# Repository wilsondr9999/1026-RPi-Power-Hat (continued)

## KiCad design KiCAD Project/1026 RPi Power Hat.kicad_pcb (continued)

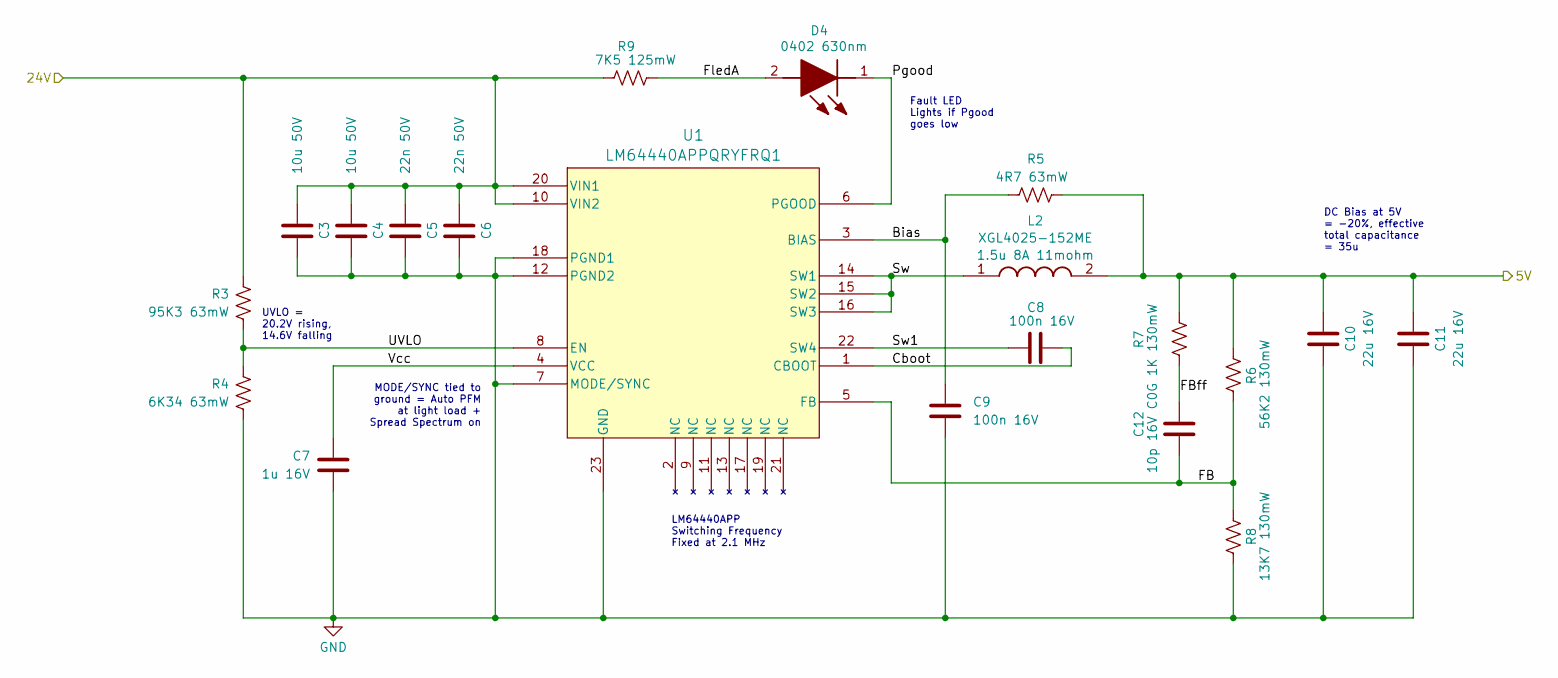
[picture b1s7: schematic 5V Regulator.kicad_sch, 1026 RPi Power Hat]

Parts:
C3, C4: GRJ32ER71H106KE11K; C_1210_3225Metric; Manufacturer_Part_Number GRJ32ER71H106KE11K; Mouser Part Number 81-GRJ32ER71H106KE1K
C5, C6: GCM155R71H223KA55D; C_0402_1005Metric; Manufacturer_Part_Number GCM155R71H223KA55D; Mouser Part Number 81-GCM155R71H223KA5D
C7: GCM188R71C105KA64J; C_0603_1608Metric; Manufacturer_Part_Number GCM188R71C105KA64J; Mouser Part Number 81-GCM188R71C105KA4J
C8, C9: GCM155R71C104KA55D; C_0402_1005Metric; Manufacturer_Part_Number GCM155R71C104KA55D; Mouser Part Number 81-GCM155R71C104KA5D
C10, C11: GCM32ER71C226ME19L; C_1210_3225Metric; Manufacturer_Part_Number GCM32ER71C226ME19L; Mouser Part Number 81-GCM32ER71C226ME9L
C12: VJ0402A100GXJCW1BC; C_0402_1005Metric; Manufacturer_Part_Number VJ0402A100GXJCW1BC; Mouser Part Number 77-VJ0402A100GXJCBC
D4: 150040RS73240; [D] Wurth Elektronik 150040RS73240; Mouser Part Number 710-150040RS73240
L2: XGL4025-152ME; [L] Coilcraft Inductor XGL4025; Manufacturer_Part_Number XGL4025-152ME
R3: 95K3; R_0402_1005Metric; Manufacturer_Part_Number CRCW040295K3FKED; Mouser Part Number 71-CRCW0402-95.3K-E3
R4: 6K34; R_0402_1005Metric; Manufacturer_Part_Number CRCW04026K34FKEDC; Mouser Part Number 71-CRCW04026K34FKEDC
R5: 4R7; R_0402_1005Metric; Manufacturer_Part_Number CRCW04024R70FNED; Mouser Part Number 71-CRCW04024R70FNED
R6: 56K2; R_0402_1005Metric; Manufacturer_Part_Number TNPW040256K2BEED; Mouser Part Number 71-TNPW040256K2BEED
R7: 1K; R_0402_1005Metric; Manufacturer_Part_Number TNPW04021K00BEED; Mouser Part Number 71-TNPW04021K00BEED
R8: 13K7; R_0402_1005Metric; Manufacturer_Part_Number TNPW040213K7BEED; Mouser Part Number 71-TNPW040213K7BEED
R9: 7K5; R_0402_1005Metric; Manufacturer_Part_Number RCC04027K50FKED; Mouser Part Number 71-RCC04027K50FKED
U1: LM64440APPQRYFRQ1; [U] TI LM63460 Sw Volt Reg; Manufacturer_Part_Number LM64440APPQRYFRQ1; Mouser Part Number 595-LM64440APPQRYRQ1

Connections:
/5V Regulator/5V: C10.1, C11.1, L2.2, R5.2, R6.1, R7.1; also elsewhere on the board
/5V Regulator/24V: C3.1, C4.1, C5.1, C6.1, R3.1, R9.1, U1.10 (VIN2), U1.20 (VIN1); also elsewhere on the board
/5V Regulator/Bias: C9.2, R5.1, U1.3 (BIAS)
/5V Regulator/Cboot: C8.2, U1.1 (CBOOT)
/5V Regulator/FB: C12.1, R6.2, R8.2, U1.5 (FB)
/5V Regulator/FBff: C12.2, R7.2
/5V Regulator/FledA: D4.2 (A), R9.2
/5V Regulator/Pgood: D4.1 (K), U1.6 (PGOOD)
/5V Regulator/Sw: L2.1, U1.14 (SW1), U1.15 (SW2), U1.16 (SW3)
/5V Regulator/Sw1: C8.1, U1.22 (SW4)
/5V Regulator/UVLO: R3.2, R4.1, U1.8 (EN)
/5V Regulator/Vcc: C7.1, U1.4 (VCC)
GND: C3.2, C4.2, C5.2, C6.2, C7.2, C9.1, C10.2, C11.2, R4.2, R8.1, U1.7 (MODE/SYNC), U1.12 (PGND2), U1.18 (PGND1), U1.23 (GND); also elsewhere on the board

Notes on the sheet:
MODE/SYNC tied to ground = Auto PFM at light load + Spread Spectrum on
Fault LED Lights if Pgood goes low
DC Bias at 5V = -20%, effective total capacitance = 35u
LM64440APP Switching Frequency Fixed at 2.1 MHz
UVLO = 20.2V rising, 14.6V falling

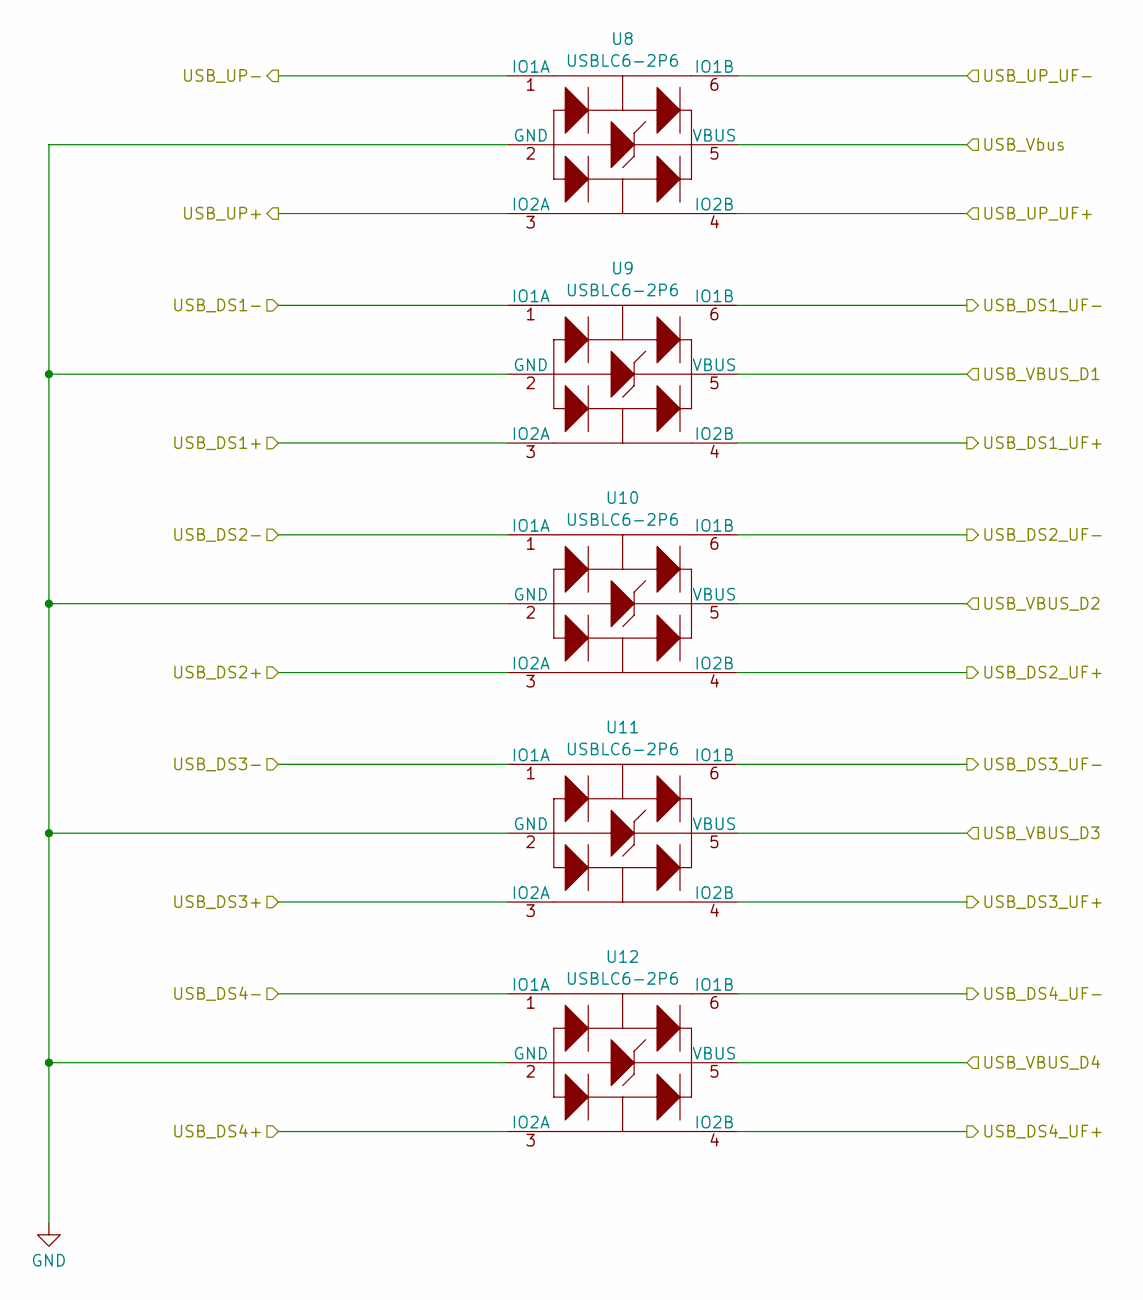
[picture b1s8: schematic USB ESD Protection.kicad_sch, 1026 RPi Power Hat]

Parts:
U8, U9, U10, U11, U12: USBLC6-2P6; [U] ST Micro USB ESD Protection USBLC6-2P6; Manufacturer_Part_Number USBLC6-2P6; Mouser Part Number 511-USBLC6-2P6

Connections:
/USB ESD Protection/USB_DS1_UF+: U9.4 (IO2B); also elsewhere on the board
/USB ESD Protection/USB_DS1_UF-: U9.6 (IO1B); also elsewhere on the board
/USB ESD Protection/USB_DS2_UF+: U10.4 (IO2B); also elsewhere on the board
/USB ESD Protection/USB_DS2_UF-: U10.6 (IO1B); also elsewhere on the board
/USB ESD Protection/USB_DS3_UF+: U11.4 (IO2B); also elsewhere on the board
/USB ESD Protection/USB_DS3_UF-: U11.6 (IO1B); also elsewhere on the board
/USB ESD Protection/USB_DS4_UF+: U12.4 (IO2B); also elsewhere on the board
/USB ESD Protection/USB_DS4_UF-: U12.6 (IO1B); also elsewhere on the board
/USB ESD Protection/USB_UP_UF+: U8.4 (IO2B); also elsewhere on the board
/USB ESD Protection/USB_UP_UF-: U8.6 (IO1B); also elsewhere on the board
/USB ESD Protection/USB_VBUS_D1: U9.5 (VBUS); also elsewhere on the board
/USB ESD Protection/USB_VBUS_D2: U10.5 (VBUS); also elsewhere on the board
/USB ESD Protection/USB_VBUS_D3: U11.5 (VBUS); also elsewhere on the board
/USB ESD Protection/USB_VBUS_D4: U12.5 (VBUS); also elsewhere on the board
/USB Hub/USB_DS1+: U9.3 (IO2A); also elsewhere on the board
/USB Hub/USB_DS1-: U9.1 (IO1A); also elsewhere on the board
/USB Hub/USB_DS2+: U10.3 (IO2A); also elsewhere on the board
/USB Hub/USB_DS2-: U10.1 (IO1A); also elsewhere on the board
/USB Hub/USB_DS3+: U11.3 (IO2A); also elsewhere on the board
/USB Hub/USB_DS3-: U11.1 (IO1A); also elsewhere on the board
/USB Hub/USB_DS4+: U12.3 (IO2A); also elsewhere on the board
/USB Hub/USB_DS4-: U12.1 (IO1A); also elsewhere on the board
/USB Hub/USB_UP+: U8.3 (IO2A); also elsewhere on the board
/USB Hub/USB_UP-: U8.1 (IO1A); also elsewhere on the board
/USB Hub/USB_Vbus: U8.5 (VBUS); also elsewhere on the board
GND: U8.2 (GND), U9.2 (GND), U10.2 (GND), U11.2 (GND), U12.2 (GND); also elsewhere on the board

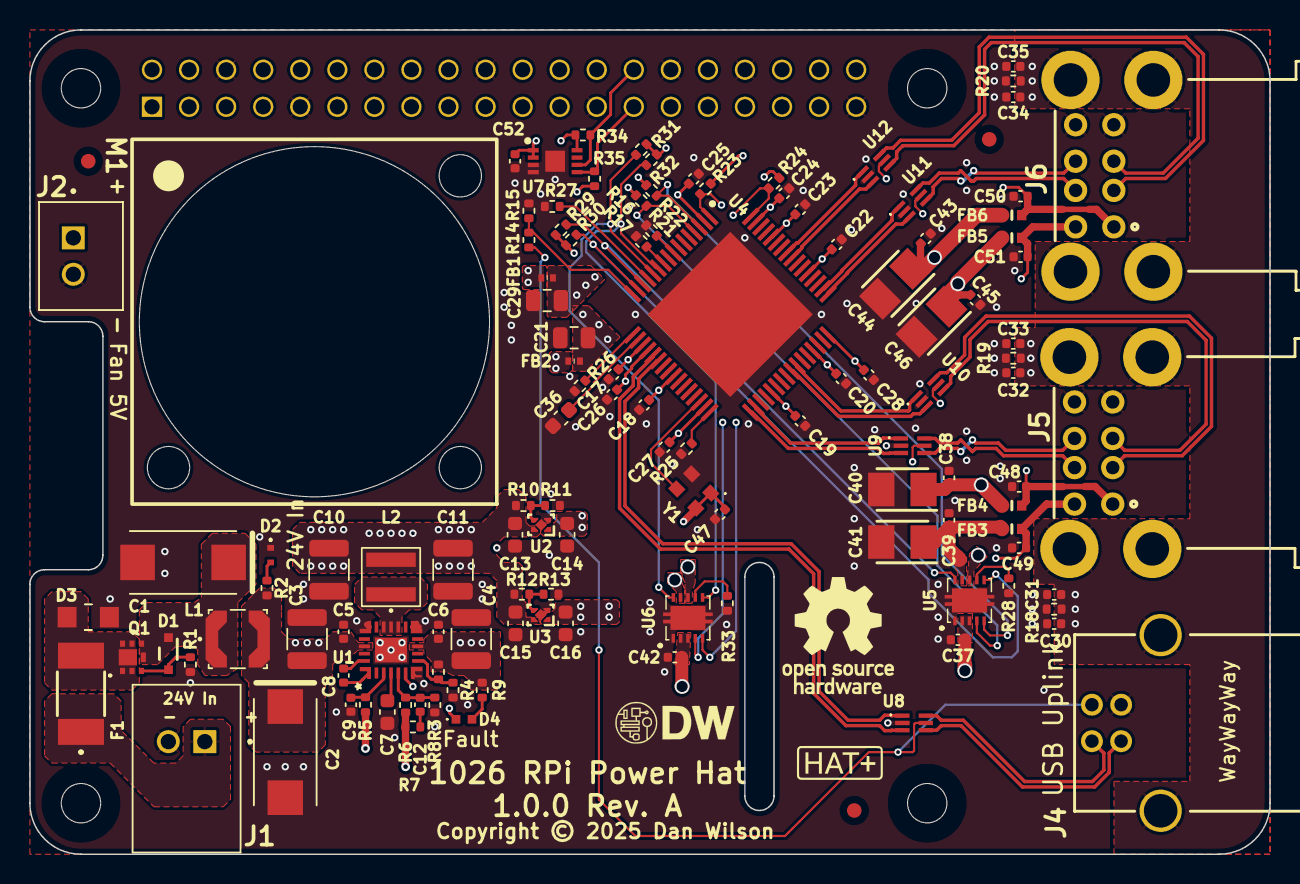
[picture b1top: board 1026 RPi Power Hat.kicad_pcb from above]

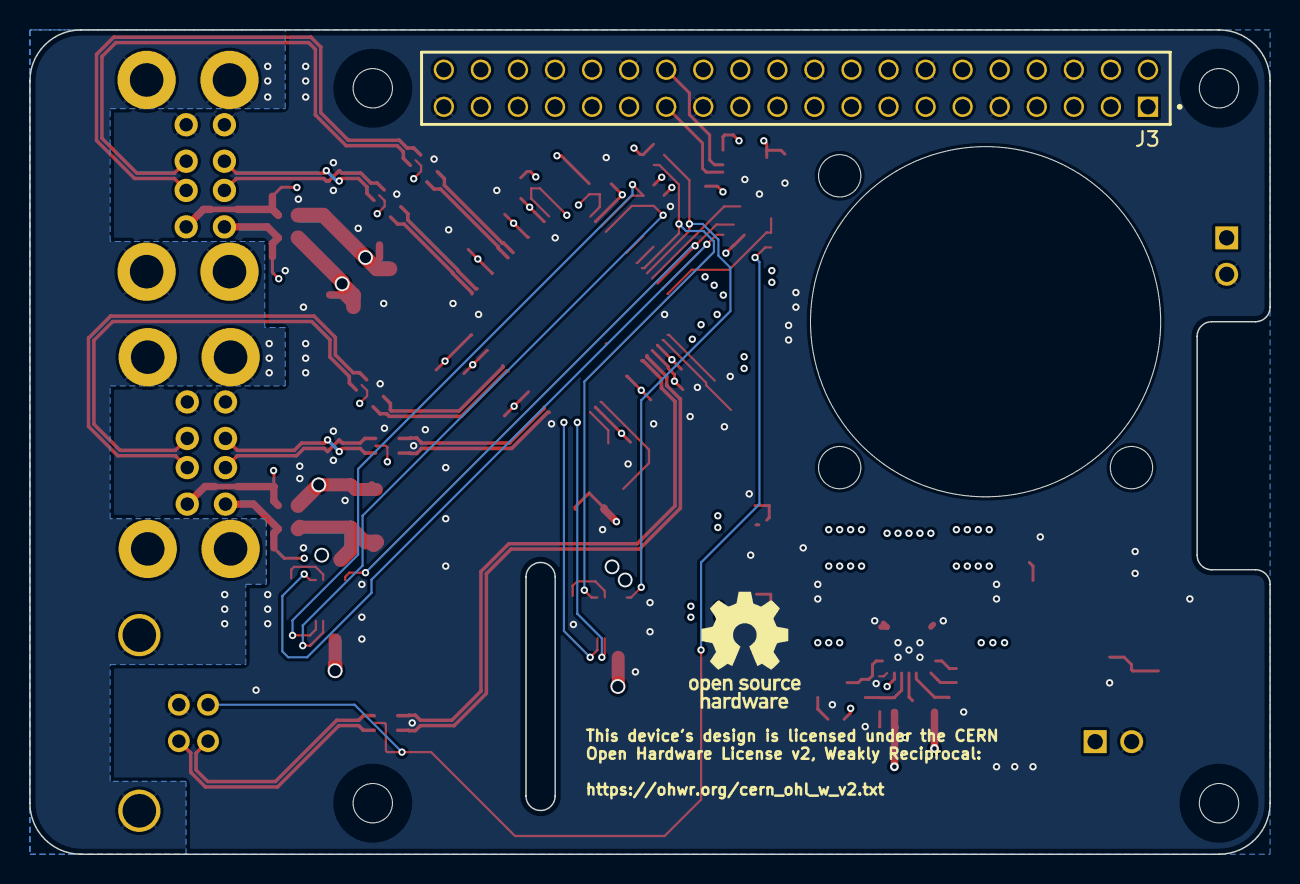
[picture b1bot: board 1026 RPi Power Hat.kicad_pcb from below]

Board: 4 copper layers, 85.0 x 56.5 mm, 132 parts (2 on the bottom side), 74 nets.

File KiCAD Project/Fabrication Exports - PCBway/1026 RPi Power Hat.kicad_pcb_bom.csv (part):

Designator,Quantity,Value,Footprint,Package,MPN,DNP,Mount_Type,Description,Height,Mouser Part Number,Mouser Price/Stock,Manufacturer_Name,Spec,DigiKey_Part_Number,Mouser Product/Spec
"C1, C2",2,T521D336M035ATE065,[C] Kemet Tantalum Polymer T521X,,T521D336M035ATE065,,smt,Input Filter Cap Tant Poly,4.3,80-T521D336M35ATE65,https://www.mouser.com/ProductDetail/KEMET/T521D336M035ATE06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,KEMET,33u 35V,,
"C10, C11",2,GCM32ER71C226ME19L,C_1210_3225Metric,,GCM32ER71C226ME19L,,smt,Output Capacitor,2.7,81-GCM32ER71C226ME9L,https://www.mouser.com/ProductDetail/Murata-Electronics/GCM3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,Murata,22u 16V,,
C12,1,VJ0402A100GXJCW1BC,C_0402_1005Metric,,VJ0402A100GXJCW1BC,,smt,Cff Capacitor,0.5,77-VJ0402A100GXJCBC,https://www.mouser.com/ProductDetail/77-VJ0402A100GXJCBC,Vishay,10p 16V C0G,,
"C13, C14, C15, C16, C36, C7",6,GCM188R71C105KA64J,C_0603_1608Metric,,GCM188R71C105KA64J,,smt,Vcc Capacitor,0.9,81-GCM188R71C105KA4J,https://www.mouser.com/ProductDetail/Murata-Electronics/GCM1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,Murata,1u 16V,,
"C17, C18, C19, C20, C22, C23, C24, C25, C26, C27, C28, C37, C38, C39, C42, C43, C45, C47, C48, C49, C50, C51, C52, C8, C9",25,GCM155R71C104KA55D,C_0402_1005Metric,,GCM155R71C104KA55D,,smt,Cboot Capacitor,0.55,81-GCM155R71C104KA5D,https://www.mouser.com/ProductDetail/Murata-Electronics/GCM1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,Murata,100n 16V,,
"C21, C29",2,GCM21BR70J106KE22K,C_0805_2012Metric,,GCM21BR70J106KE22K,,smt,3V3 Bus Capacitor,1.4,81-GCM21BR70J106KE2K,https://www.mouser.com/ProductDetail/Murata-Electronics/GCM2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,Murata,10u 6V3,,
"C3, C4",2,GRJ32ER71H106KE11K,C_1210_3225Metric,,GRJ32ER71H106KE11K,,smt,Input Capacitor,2.8,81-GRJ32ER71H106KE1K,https://www.mouser.com/ProductDetail/Murata-Electronics/GRJ3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,Murata,10u 50V,,
"C30, C33, C35",3,GCM155R71H104KE02J,C_0402_1005Metric,,GCM155R71H104KE02J,,smt,USB Shield EMI Cap,0.55,81-GCM155R71H104KE2J,https://www.mouser.com/ProductDetail/Murata-Electronics/GCM1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,Murata,100n 50V,,
"C31, C32, C34",3,GCM155R71H102KA37D,C_0402_1005Metric,,GCM155R71H102KA37D,,smt,USB Shield EMI Cap,0.55,81-GCM155R71H102KA7D,https://www.mouser.com/ProductDetail/Murata-Electronics/GCM1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,Murata,1n 50V,,
"C40, C41, C44, C46",4,TCJB157M006R0070,[C] Kyocera AVC Tant Poly TCJB157M006R0070,,TCJB157M006R0070,,smt,"AVX 150uF SMD Solid Polymer Tantalum Electrolytic Capacitor, 6.3 V dc +/-20%, TCJ Series",2.1,581-TCJB157M006R0070,https://www.mouser.com/ProductDetail/KYOCERA-AVX/TCJB157M006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,Kyocera AVX,150u 6V3,,
"C5, C6",2,GCM155R71H223KA55D,C_0402_1005Metric,,GCM155R71H223KA55D,,smt,Input Capacitor,0.55,81-GCM155R71H223KA5D,https://www.mouser.com/ProductDetail/Murata-Electronics/GCM1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,Murata,22n 50V,,
D1,1,"PDZ10B,115","[D] Nexperia Zener PDZ10B,115 10V",,"PDZ10B,115",,smt,Rev Power Prot Diode,1.1,771-PDZ10B115,https://www.mouser.com/ProductDetail/Nexperia/PDZ10B115?qs=L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,Nexperia,10V 2% 400mW,,
D2,1,150040GS73220,[D] Wurth Elektronik 150040GS73220,,150040GS73220,,smt,Input Power LED,0.35,710-150040GS73220,https://www.mouser.com/ProductDetail/Wurth-Elektronik/150040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,Wurth Elektronik,0603 525nm,,
D3,1,SMF24CA,[D] Littelfuse SMF24CA 24V 200W,,SMF24CA,,smt,Input TVS Surge Suppression,1.08,576-SMF24CA,https://www.mouser.com/ProductDetail/Littelfuse/SMF24CA?qs=d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,Littelfuse,TVS BiDir 24V 200W,,
D4,1,150040RS73240,[D] Wurth Elektronik 150040RS73240,,150040RS73240,,smt,Fault LED,0.5,710-150040RS73240,https://www.mouser.co.uk/ProductDetail/Wurth-Elektronik/1500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,Wurth Elektronik,0402 630nm,,
F1,1,1812L110/33MR,[F] Littelfuse PPTC 1812L010DR,,1812L110/33MR,,smt,Input PPTC Resettable Fuse,1.25,576-1812L110/33MR,https://www.mouser.com/ProductDetail/Littelfuse/1812L110-33M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,LITTELFUSE,1.1A 33V,,
"FB1, FB2",2,BLM15PX221SZ1D,[FB] Murata BLM15PX221SZ1D,,BLM15PX221SZ1D,,smt,BLM15_Z1D Series EMI Suppression Filter 220+/-25% at 100MHz 1.4A @85,0.55,81-BLM15PX221SZ1D,https://www.mouser.com/ProductDetail/Murata-Electronics/BLM1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,Murata Electronics,220 ohm 100MHz,,
"FB3, FB4, FB5, FB6",4,BLM18KG221SN1D,[FB] Murata BLM18KG221SN1D 220ohm 2.2A,,BLM18KG221SN1D,,smt,BLM18 Series EMI Suppression Filter 220+/-25% at 100MHz 2.2A @85,0.55,81-BLM18KG221SN1D,https://www.mouser.com/ProductDetail/Murata-Electronics/BLM1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,Murata Electronics,220ohm 2.2A,,
J1,1,S2B-XH-A-1,[J] JST S2B-XH-A-1,,S2B-XH-A-1,,tht,Input Power Connector,7 mm,306-S2BXHA1LFSN,https://www.mouser.com/ProductDetail/JST-Commercial/S2B-XH-A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,JST,JST-XH-2 Side,455-S2B-XH-A-1-ND,
J2,1,B2B-XH-A(LF)(SN),JST_B2B-XH-A(LF)(SN),,B2B-XH-A(LF)(SN),,tht,Connector Header Through Hole 2 position 0.098 (2.50mm),7 mm,306-B2BXHALFSNP,https://www.mouser.com/ProductDetail/JST-Commercial/B2B-XH-A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,JST,JST-XH-2,455-B2B-XH-A-ND,
J3,1,ESW-120-34-G-D,[J] Samtec Elevated Socket Strip ESW-120-34-G-D,,ESW-120-34-G-D,,tht,Elevated Socket Strip 0.28in 20x2 16.13mmH Gold,16.13,200-ESW12034GD,https://www.mouser.com/ProductDetail/Samtec/ESW-120-34-G-D?q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,Samtec,"20x2 0.28"" Header",,
J4,1,USB1030-GF-P-B-B,[J] GCT USB-B 2.0 Connector PCB USB1030-GF-P-B-B,,USB1030-GF-P-B-B,,tht,"USB Connectors USB B Skt, TH, GF, USB-B 2.0",10.95,640-USB1030-GF-P-B-B,https://www.mouser.com/ProductDetail/GCT/USB1030-GF-P-B-B?qs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,GCT,"USB Connectors USB B Skt, TH, GF, USB-B 2.0",,
"J5, J6",2,USB1035-GF-P-0-B-B,[J] GCT USB-A x2 2.0 Connector USB1035-GF-P-0-B-B,,USB1035-GF-P-0-B-B,,tht,"USB-A (USB TYPE-A), Stacked USB 2.0 Receptacle Connector 8 Position Through Hole, Right Angle",15.32,640-USB1035GFP0BB,https://www.mouser.com/ProductDetail/GCT/USB1035-GF-P-0-B-B?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,GCT,"USB Connectors USB A Skt, TH, GF, USB-A 2.0",,
L1,1,LPS4040-223,[L] Coilcraft Inductor LPS4040,,LPS4040-223,,smt,Input Filter Inductor,4,,,Coilcraft,22uH 0.8A 210mohm,,
L2,1,XGL4025-152ME,[L] Coilcraft Inductor XGL4025,,XGL4025-152ME,,smt,SMPS Buck Inductor,2.5,,,Coilcraft,1.5u 8A 11mohm,,
M1,1,CFM-2510B-070-140,[Fan] SameSky CFM-2510B-070-140,,CFM-2510B-070-140,,smt,"DC Fans dc axial fan, 25 mm square, 10 mm, 5 Vdc, omniCOOL, 5000 RPM, 1.35 CFM",10,490-CFM2510B-070-140,https://www.mouser.com/ProductDetail/Same-Sky/CFM-2510B-070-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,Same Sky,5V 7000RPM 25mm,,
Q1,1,BUK6D120-60PX,[Q] Nexperia BUK6D120-60PX P-Ch 60V 8A,,BUK6D120-60PX,,smt,Rev Power Prot MOSFET,0.65,771-BUK6D120-60PX,https://www.mouser.com/ProductDetail/Nexperia/BUK6D120-60PX?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,Nexperia,P-Ch 60V 8A,,
R1,1,15K,R_0402_1005Metric,,CRCW040215K0FKED,,smt,Rev Power Prot Zener Resistor,0.40,71-CRCW0402-15K-E3,https://www.mouser.com/ProductDetail/Vishay-Dale/CRCW040215K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,Vishay,15K 63mW,,
R10,1,12K7,R_0402_1005Metric,,CRCW040212K7FKED,,smt,1V1 UVLO Rt,0.35,71-CRCW0402-12.7K-E3,https://www.mouser.com/ProductDetail/Vishay-Dale/CRCW040212K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,Vishay,12K7 63mW,,
"R11, R29, R30, R31, R32",5,10K,R_0402_1005Metric,,CRCW040210K0FKEDC,,smt,"[R11]1V1 UVLO Rb; [R29,R30,R31,R32]Pull Up Resistor",0.35,71-CRCW040210K0FKEDC,https://www.mouser.com/ProductDetail/Vishay-Dale/CRCW040210K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,Vishay,10K 63mW,,
R12,1,26K7,R_0402_1005Metric,,CRCW040226K7FKED,,smt,3V3 UVLO Rt,0.40,71-CRCW0402-26.7K-E3,https://www.mouser.com/ProductDetail/Vishay-Dale/CRCW040226K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,Vishay,26K7 63mW,,
R13,1,10K2,R_0402_1005Metric,,CRCW040210K2FKED,,smt,1V1 UVLO Rt,0.40,71-CRCW0402-10.2K-E3,https://www.mouser.com/ProductDetail/Vishay-Dale/CRCW040210K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,Vishay,10K2 63mW,,
R14,1,90K9,R_0402_1005Metric,,TNPW040290K9BEED,,smt,Vbus Sense Resistor Top,0.40,71-TNPW040290K9BEED,https://www.mouser.com/ProductDetail/Vishay-Dale/TNPW040290K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,Vishay,90K9 130mW,,
R15,1,10K,R_0402_1005Metric,,TNPW040210K0BEED,,smt,Vbus Sense Resistor Bottom,0.40,71-TNPW040210K0BEED,https://www.mouser.com/ProductDetail/Vishay-Dale/TNPW040210K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,Vishay,10K 130mW,,
"R16, R17, R21, R22, R23, R24, R26, R27",8,4K7,R_0402_1005Metric,,CRCW04024K70FKEDC,,smt,"[R26,R27]Pull Down Resistor; [R21,R22,R23,R24]Pull Up Resistor",0.35,71-CRCW04024K70FKEDC,https://www.mouser.com/ProductDetail/Vishay-Dale/CRCW04024K7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,Vishay,4K7 63mW,,
"R18, R19, R20",3,1M,R_0402_1005Metric,,CRCW04021M00FKED,,smt,Pull Down Resistor,0.35,71-CRCW0402-1.0M-E3,https://www.mouser.com/ProductDetail/Vishay-Dale/CRCW04021M0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 ,Vishay,1M 63mW,,
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
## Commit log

2025-04-21 v1.0.0 RC
    v1.0.0 of 1026 Raspberry Pi Power HAT, candidate for initial production.
2025-04-21 v1.0.0 RC2
    Build candidate 2
2025-05-03 v1.0.0 RC3
    Minor change to upstream USB port to connect Vbus to ESD protection vice on-board 5V.
2025-05-18 v1.0.0
    Initial Commit
2025-07-06 v1.0.0 Final
2025-07-06 v1.0.0A
    Moved all symbols, footprints, and 3D models to local project-specific libraries in /KiCAD Project/Libraries.
2025-07-09 Update .gitignore
    Update .gitignore file to exclude KiCAD auto-backups and lock files.
2025-07-22 Solder mask, parts and text updates
    Use pass through header ESW-120-34-G-D vs ESW-120-33-G-D
    Add PCBWay test WayWayWay under J4
    Change board name text to be "1026 RPi Power Hat"
    Add board version text "1.0.0 Rev A"
    Change Solder Mask clearance from 0 to -0.01 on U4 in footprint properties for PCBway minimum clearance of 0.22mm
    Change board silkscreen color to Black
2025-07-22 New BOM for new Parts
    Add ESW-120-34-G-D and remove ESW-120-33-G-D. Update BOM and iBOM.
2025-07-26 Prep for PCBway
    Verified all parts reference local libraries, update font for PCB board title to Noto Sans font, add Noto Sans fonts to project folder, update 3D image for documentation, update documentation for lin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
